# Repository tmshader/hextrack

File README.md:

# HexTrack

An open-source 3D printable trackball using the PMW3389 sensor.

# Visit website for more info: [https://hextrack.tmsahder.me](https://hextrack.tmshader.me)

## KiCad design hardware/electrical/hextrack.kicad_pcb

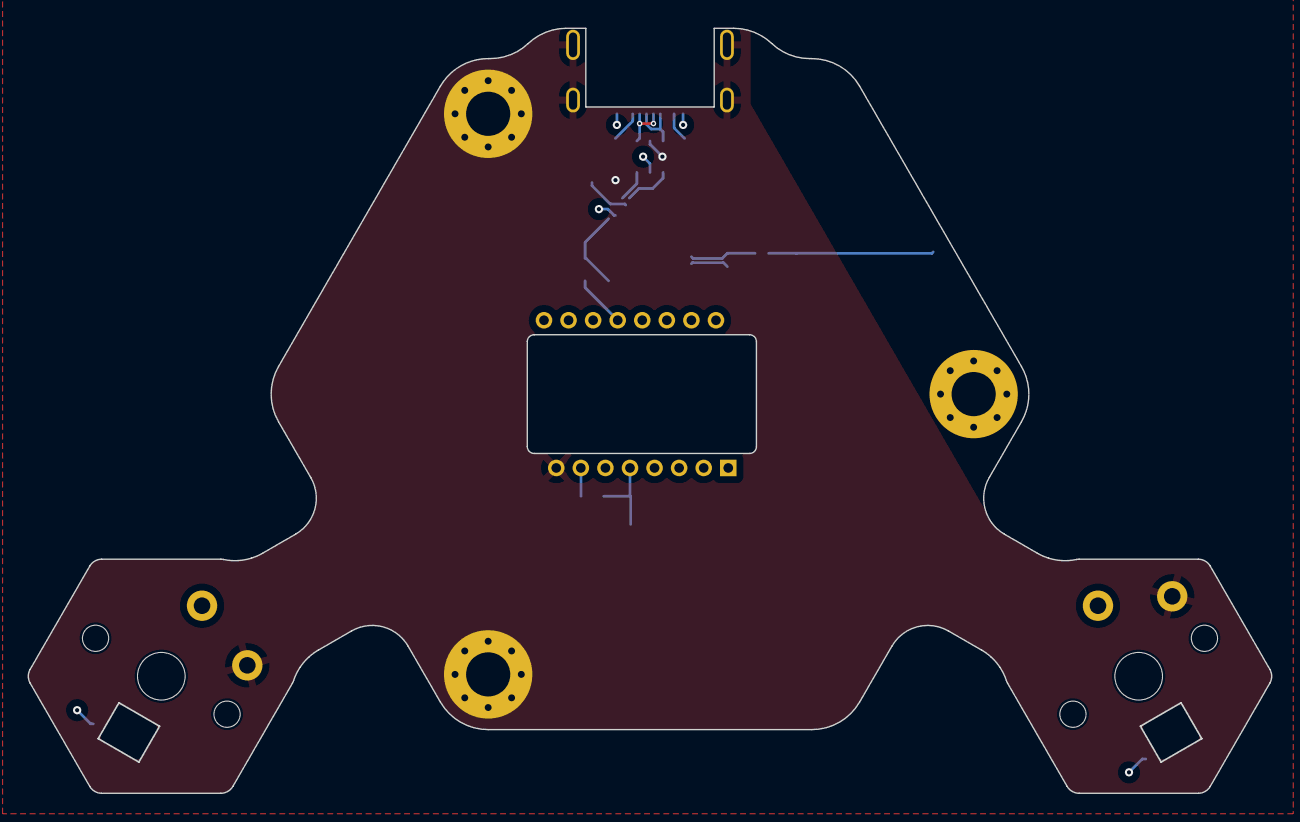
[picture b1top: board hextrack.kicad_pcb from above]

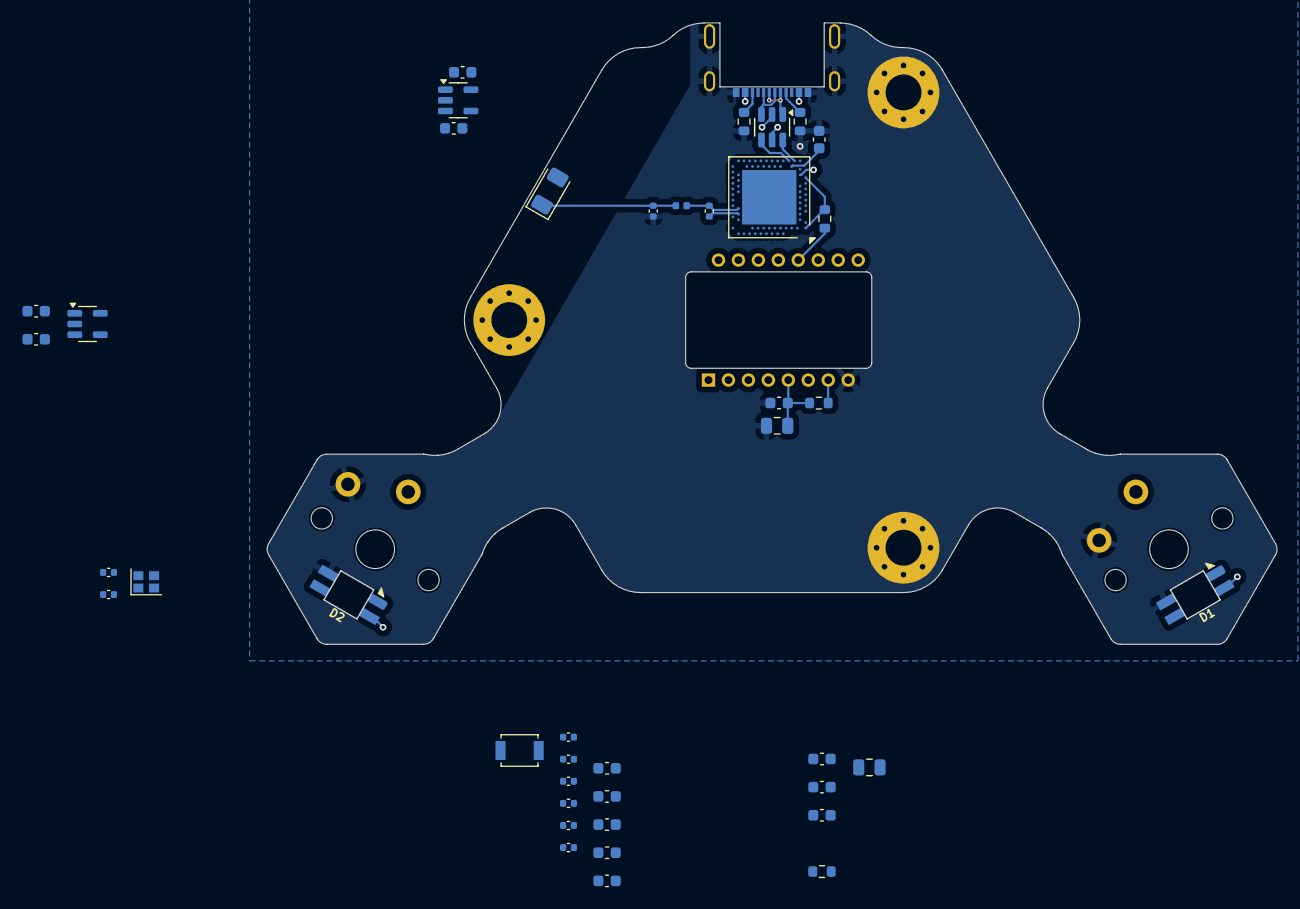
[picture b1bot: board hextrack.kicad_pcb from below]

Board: 4 copper layers, 90.1 x 55.4 mm, 48 parts (41 on the bottom side), 31 nets.

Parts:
AN1: Antenna; D_1206_3216Metric
C1, C2, C3, C4, C11, C16: 1uF; C_0603_1608Metric
C5, C9, C10, C12: 4.7uF; C_0603_1608Metric
C6: 820pF; C_0402_1005Metric
C7: 100pF; C_0402_1005Metric
C8, C13, C14, C15: 100nF; C_0402_1005Metric
C17: 0.5pF; C_0402_1005Metric
C18: 0.8pF; C_0402_1005Metric
C19, C20: 12pF; C_0402_1005Metric
C21, C24, C25: 100nF; C_0603_1608Metric
C22, C23: 10uF; C_0805_2012Metric
C26: 4.7uF 10V; C_0603_1608Metric
D1, D2: SK6812MINI-E; LED_SK6812MINI
H1, H2, H3: Mounting hole with pad; MountingHole_3.2mm_M3_Pad_Via
J1: USB Type-C Receptacle 16P; USB_C_16P_CB0.8_073
L1: 4.7nH; L_0402_1005Metric
R1, R2: 5.1k; R_0603_1608Metric
R3, R5: 10k; R_0603_1608Metric
R4: 13R; R_0603_1608Metric
S1: B3U-1000P; SW_SPST_B3U-1000P
S2, S3: Kailh Choc V1; Choc_V1
U1: USBLC6-2SC6; SOT-23-6
U2: AP2204K-1.8; SOT-23-5
U3: AP2204K-3.3; SOT-23-5
U4: nRF52840; Nordic_AQFN-73-1EP_7x7mm_P0.5mm
U5: PMW3389DM-T3QU; PixArt_PMW3389DM-T3QU
Y1: 32 MHz Crystal; Crystal_SMD_2016-4Pin_2.0x1.6mm

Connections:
+1V8: C2.2, C23.1, C24.1, R4.1, U2.5 (VOUT), U5.4 (VDD)
+3V3: C4.2, C9.2, U3.5 (VOUT), U4.AD2 (VBUS)
/Block Diagram/MCU/MISO: R5.1, U4.U24 (P1.04), U5.12 (MISO)
/Block Diagram/MCU/MOSI: U4.W24 (P1.02), U5.11 (MOSI)
/Block Diagram/MCU/MOTION: U4.AD18 (P0.22), U5.9 (MOTION)
/Block Diagram/MCU/SCLK: U4.AD20 (P0.24), U5.10 (SCLK)
/Block Diagram/MCU/USB_D+: U1.4 (I/O2), U4.AD6 (D+)
/Block Diagram/MCU/USB_D-: U1.6 (I/O1), U4.AD4 (D-)
/Block Diagram/MCU/VDD: C12.2, C13.2, C14.2, C15.2, C16.2, C21.1, C22.1, R3.2, R5.2, U4.A22 (VDD), U4.AD14 (VDD), U4.AD23 (VDD), U4.B1 (VDD), U4.W1 (VDD), U5.5 (VDDIO)
/Block Diagram/MCU/~CS: U4.R24 (P1.06), U5.13 (~CS)
/Block Diagram/MCU/~RESET: S1.2 (B), U4.AC9 (P0.14), U4.AC11 (P0.16), U4.AC13 (P0.18/~RESET)
/Block Diagram/USB-C/ND+: J1.A6 (D+), J1.B6 (D+), U1.3 (I/O2)
/Block Diagram/USB-C/ND-: J1.A7 (D-), J1.B7 (D-), U1.1 (I/O1)
GND: C1.1, C2.1, C3.1, C4.1, C5.1, C6.1, C7.1, C8.1, C9.1, C10.1, C11.1, C12.1, C13.1, C14.1, C15.1, C16.1, C17.1, C19.2, C20.2, C21.2, C22.2, C23.2, C24.2, C25.2, C26.2, D1.2 (VSS), D2.2 (VSS), H1.1, H2.1, H3.1, J1.A1 (GND), J1.A12 (GND), J1.B1 (GND), J1.B12 (GND), J1.S1 (SHIELD), R1.1, R2.1, S1.1 (A), S2.2, S3.2, U1.2 (GND), U2.2 (GND), U3.2 (GND), U4.B7 (VSS), U4.EP (VSS), U5.8 (GND)
unnamed: AN1.1 (A), C17.2, L1.1
unnamed: D1.1 (DOUT), D2.3 (DIN)
unnamed: J1.A5 (CC1), R1.2
unnamed: J1.B5 (CC2), R2.2
unnamed: C18.2, L1.2, U4.H23 (ANT)
unnamed: C8.2, U4.C1 (DEC1)
unnamed: C7.2, U4.D23 (DEC3)
unnamed: C11.2, U4.B5 (DEC4), U4.E24 (DEC6)
unnamed: C6.2, U4.N24 (DEC5)
unnamed: C5.2, U4.AC5 (DECUSB)
unnamed: C19.1, U4.B24 (XC1), Y1.2
unnamed: C20.1, U4.A23 (XC2), Y1.1
unnamed: R4.2, U5.15 (LED_P)
unnamed: C25.1, C26.1, U5.3 (VDDPIX)
unnamed: R3.1, U5.7 (~RESET)
RF_GND: C18.1, U4.F23 (VSS_PA)
VBUS: C1.2, C3.2, C10.2, D1.4 (VDD), D2.4 (VDD), J1.A4 (VBUS), J1.A9 (VBUS), J1.B4 (VBUS), J1.B9 (VBUS), U1.5 (VBUS), U2.1 (VIN), U2.3 (EN), U3.1 (VIN), U3.3 (EN), U4.Y2 (VDDH)

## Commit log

2025-02-01 Update schematic to include regulators and switches, update render
